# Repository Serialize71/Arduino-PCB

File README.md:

This is an arduino with dht11 temperature and humidity

In this design I used ATmega328p which is Through-hole microcontroller

Also connected all pins with pin sockets

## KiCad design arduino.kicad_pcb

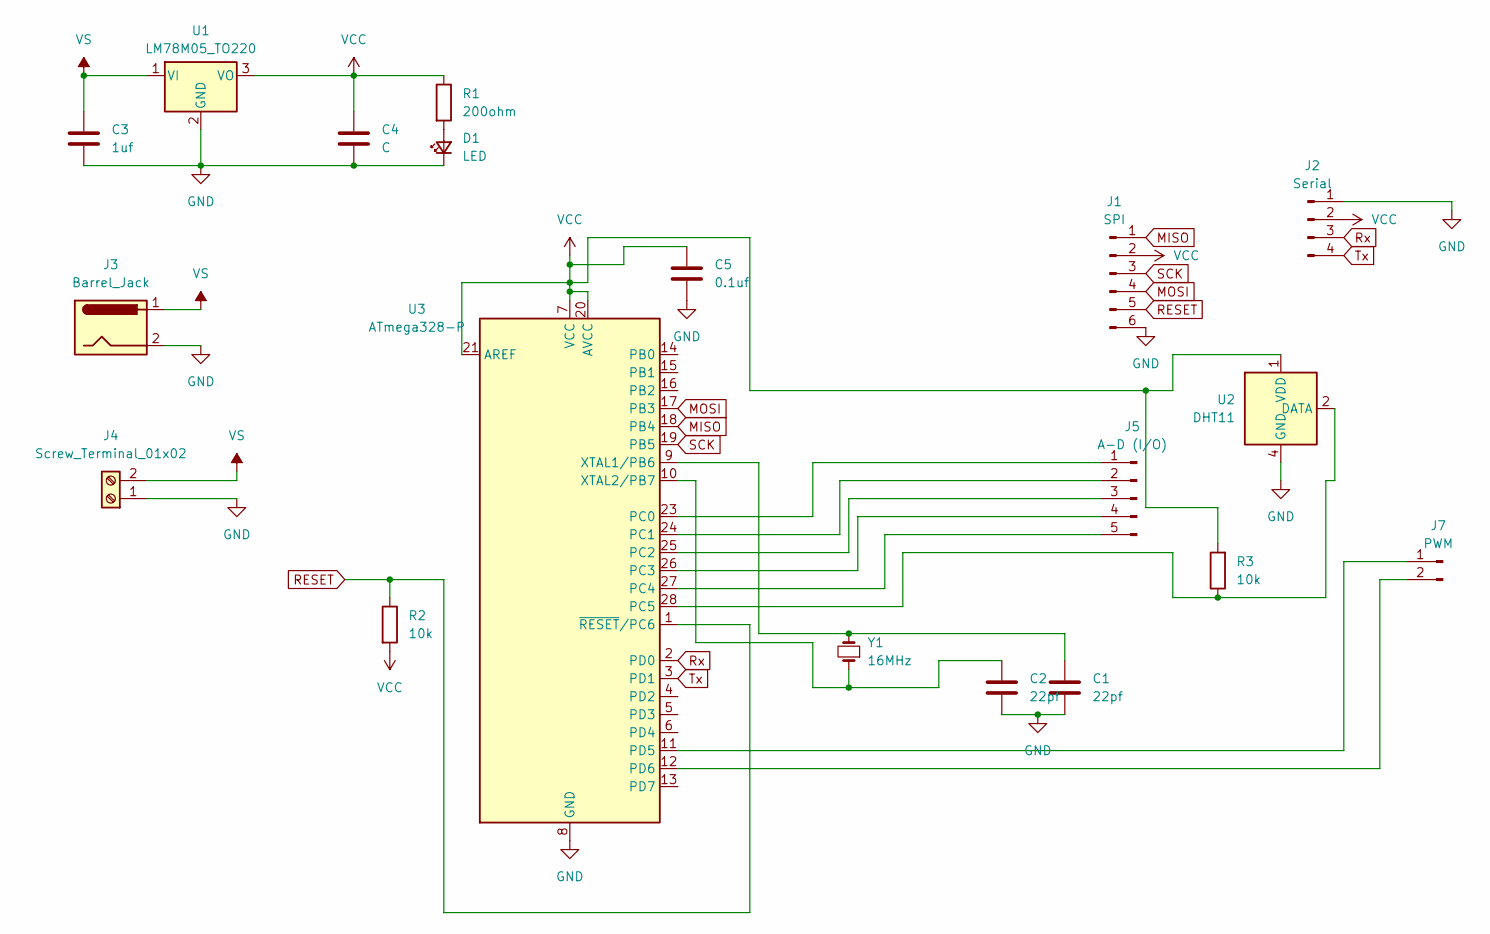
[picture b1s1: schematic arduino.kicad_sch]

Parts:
C1, C2: 22pf; C_Disc_D5.0mm_W2.5mm_P5.00mm
C3: 1uf; CP_Radial_D8.0mm_P3.50mm
C4: C; C_Disc_D5.0mm_W2.5mm_P5.00mm
C5: 0.1uf; C_Disc_D5.0mm_W2.5mm_P5.00mm
D1: LED; LED_D3.0mm
J1: SPI; PinSocket_1x06_P2.54mm_Vertical
J2: Serial; PinHeader_1x04_P2.54mm_Vertical
J3: Barrel_Jack; BarrelJack_GCT_DCJ200-10-A_Horizontal
J4: Screw_Terminal_01x02; Screw_Terminal_3.5mm-2-Blue
J5: A-D (I/O); PinSocket_1x05_P2.54mm_Vertical
J7: PWM; PinSocket_1x02_P2.54mm_Vertical
R1: 200ohm; R_Axial_DIN0204_L3.6mm_D1.6mm_P1.90mm_Vertical
R2, R3: 10k; R_Axial_DIN0204_L3.6mm_D1.6mm_P1.90mm_Vertical
U1: LM78M05_TO220; TO-220-3_Vertical
U2: DHT11; Aosong_DHT11_5.5x12.0_P2.54mm
U3: ATmega328-P; DIP-28_W7.62mm
Y1: 16MHz; Crystal_HC49-4H_Vertical

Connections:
GND: C1.2, C2.2, C3.2, C4.2, C5.2, D1.1 (K), J1.6, J2.1, J3.2, J4.1, U1.2 (GND), U2.4 (GND), U3.8 (GND), U3.22 (GND)
MISO: J1.1, U3.18 (PB4)
MOSI: J1.4, U3.17 (PB3)
unnamed: D1.2 (A), R1.2
unnamed: J5.1, U3.23 (PC0)
unnamed: J5.2, U3.24 (PC1)
unnamed: J5.3, U3.25 (PC2)
unnamed: J5.4, U3.26 (PC3)
unnamed: J5.5, U3.27 (PC4)
unnamed: J7.1, U3.11 (PD5)
unnamed: J7.2, U3.12 (PD6)
unnamed: R3.1, U2.2 (DATA), U3.28 (PC5)
unnamed: C1.1, U3.9 (XTAL1/PB6), Y1.2
unnamed: C2.1, U3.10 (XTAL2/PB7), Y1.1
RESET: J1.5, R2.1, U3.1 (~RESET/PC6)
Rx: J2.3, U3.2 (PD0)
SCK: J1.3, U3.19 (PB5)
Tx: J2.4, U3.3 (PD1)
VCC: C4.1, C5.1, J1.2, J2.2, R1.1, R2.2, R3.2, U1.3 (VO), U2.1 (VDD), U3.7 (VCC), U3.20 (AVCC), U3.21 (AREF)
VS: C3.1, J3.1, J4.2, U1.1 (VI)

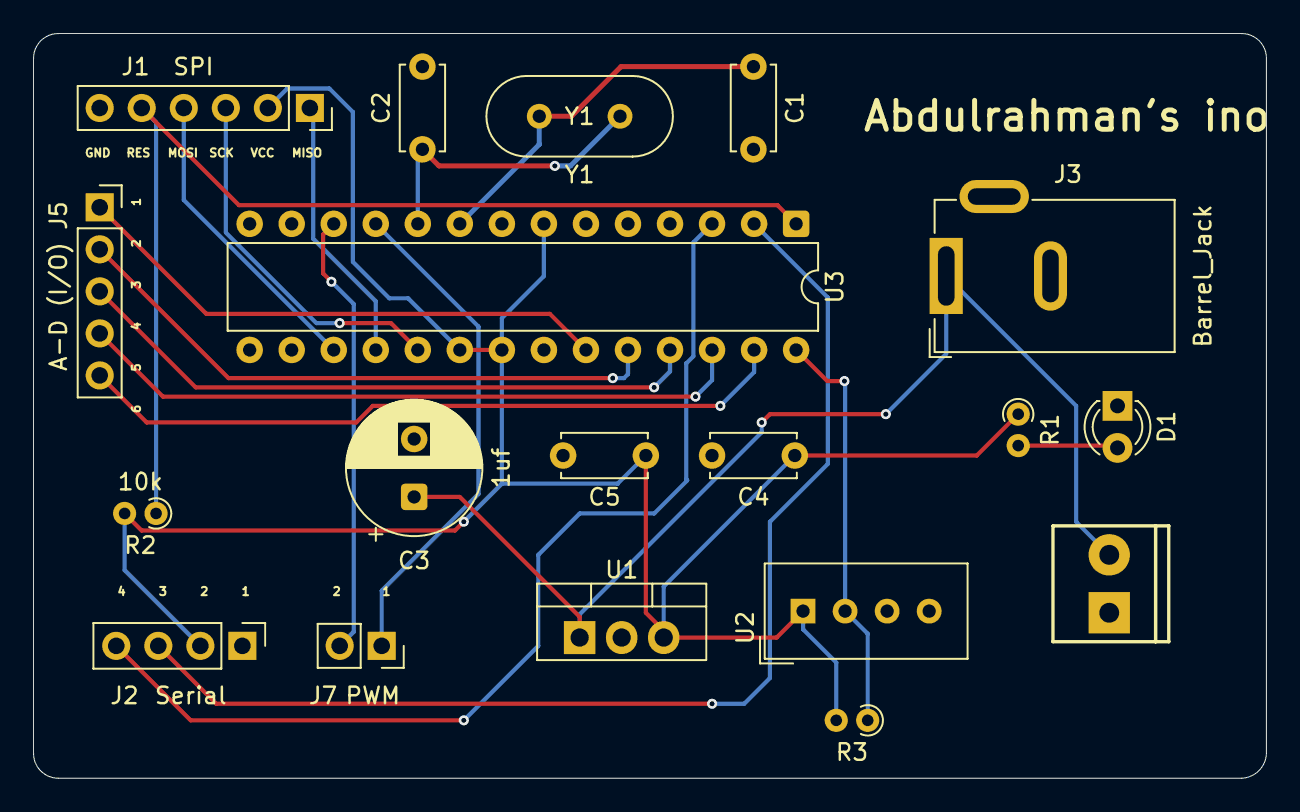
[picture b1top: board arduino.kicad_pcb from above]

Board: 2 copper layers, 74.5 x 45.0 mm, 19 parts (0 on the bottom side), 20 nets.

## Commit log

2025-06-26 creating repo
2025-06-26 adding photos
